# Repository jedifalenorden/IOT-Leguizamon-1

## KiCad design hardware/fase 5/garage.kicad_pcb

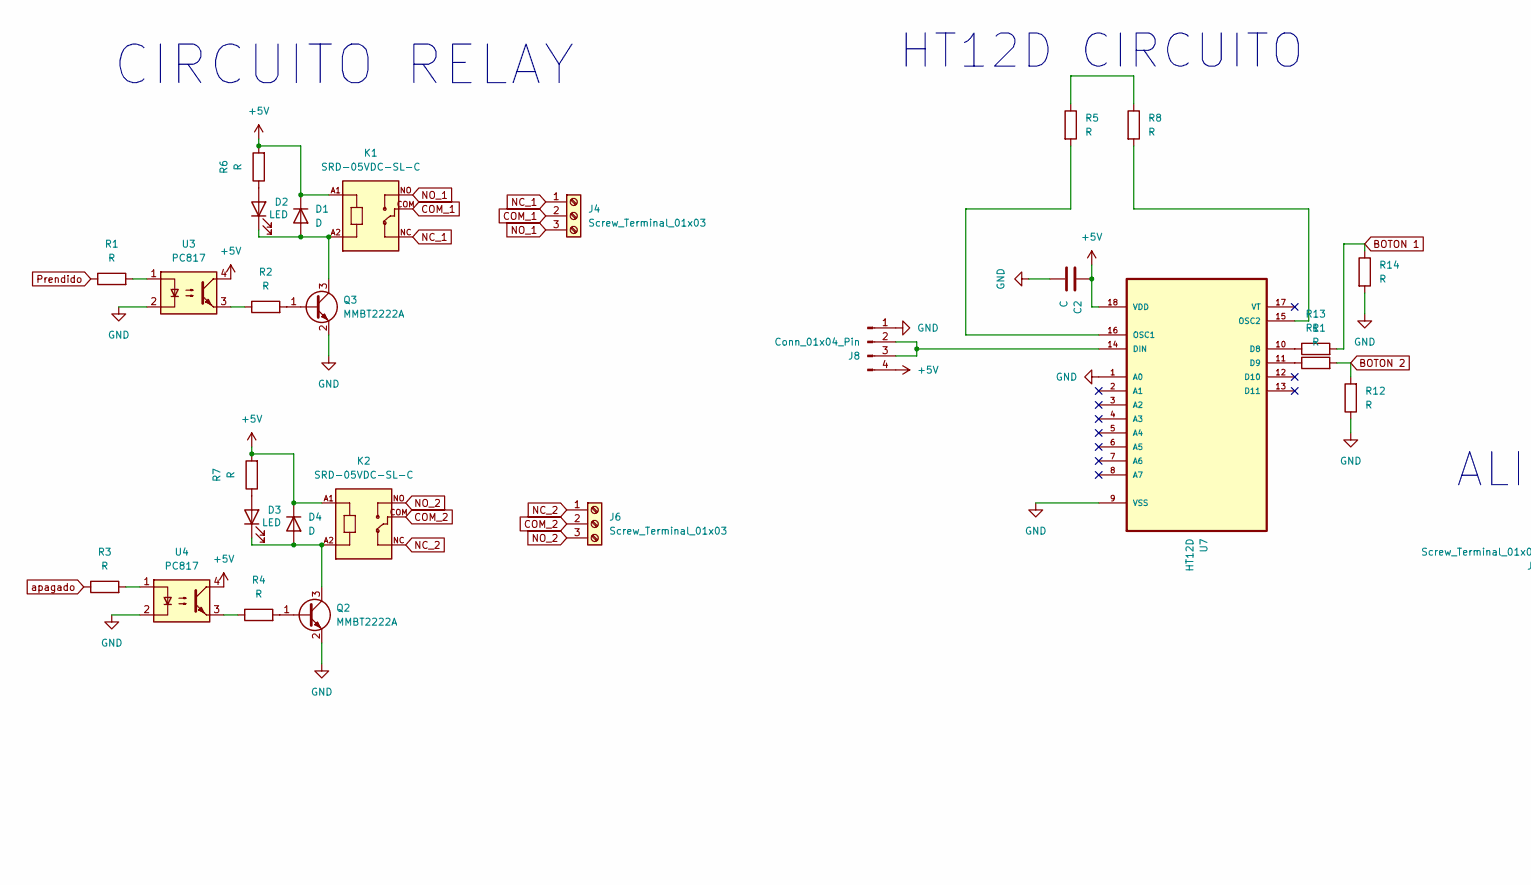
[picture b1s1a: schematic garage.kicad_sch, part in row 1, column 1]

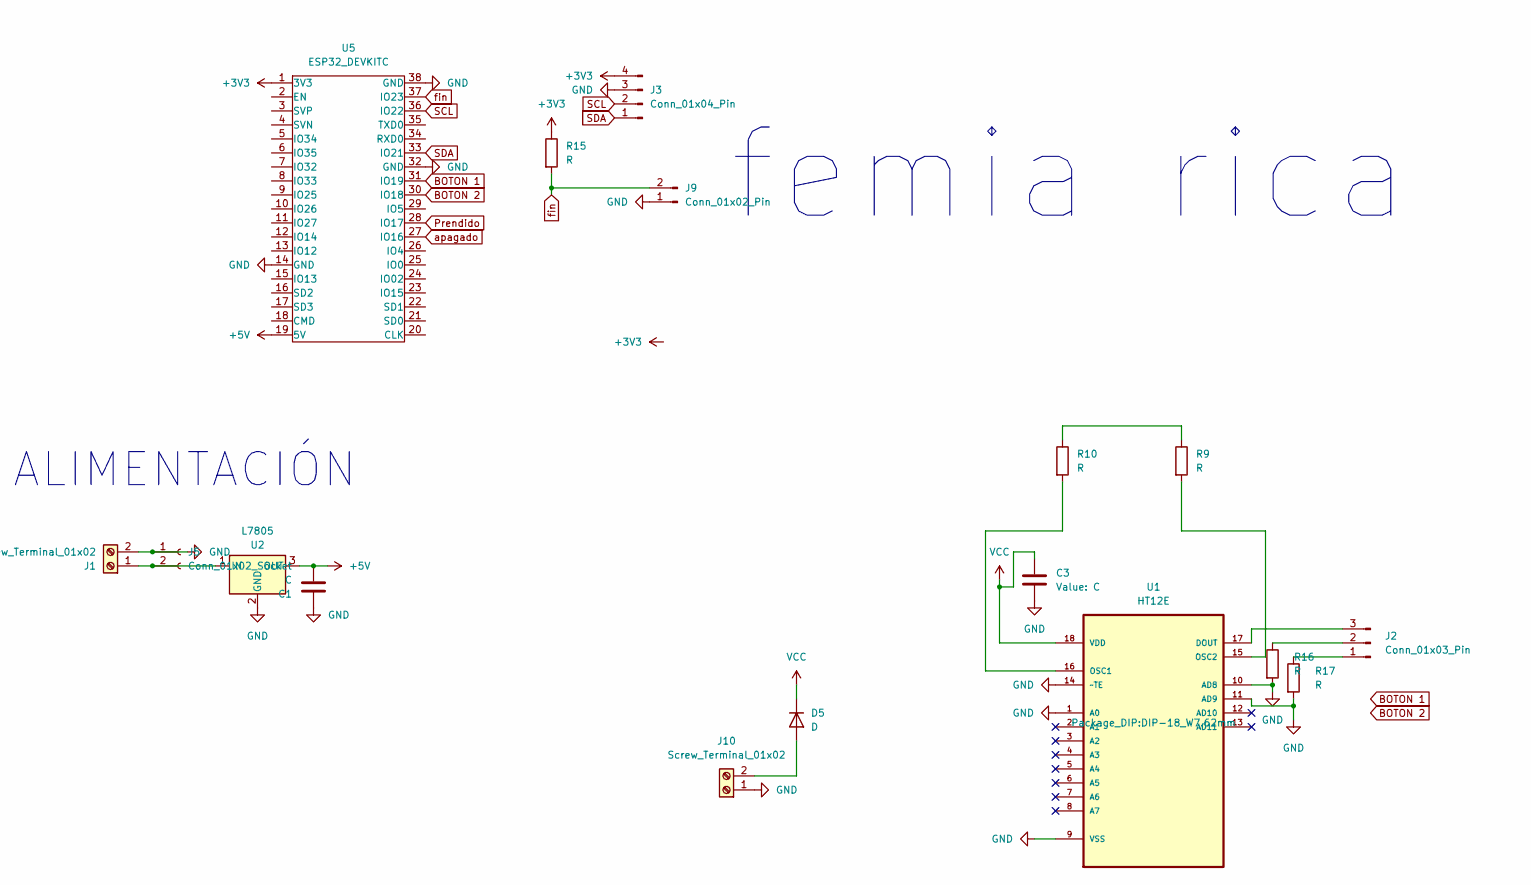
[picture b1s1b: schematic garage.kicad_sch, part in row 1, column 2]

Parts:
C1, C2, C3: C; C_0805
D1, D4: D; DO-41
D2, D3: LED; LED_D3.0mm
D5: D; D_0805_2012Metric
J1: Screw_Terminal_01x02; AMASS_XT30U-F_1x02_P5.0mm_Vertical
J2: Conn_01x03_Pin; PinHeader_1x03_P2.54mm_Vertical
J3, J8: Conn_01x04_Pin; PinHeader_1x04_P2.54mm_Vertical
J4, J6: Screw_Terminal_01x03; TerminalBlock_MetzConnect_Type011_RT05503HBWC_1x03_P5.00mm_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
J5: Conn_01x02_Socket; PinHeader_1x02_P2.00mm_Vertical
J9: Conn_01x02_Pin; PinHeader_1x02_P2.54mm_Vertical
J10: Screw_Terminal_01x02; BORNERA2_AZUL
K1, K2: SRD-05VDC-SL-C; RELAY_SRD-05VDC-SL-C
Q2, Q3: MMBT2222A; SOT-23
R1, R2, R3, R4, R5, R6, R7, R8, R9, R10, R11, R12, R13, R14, R15, R16, R17: R; R_0805
U1: HT12E; DIP-18_W7.62mm; MPN HT12E
U2: L7805; TO-263-3_TabPin2
U3, U4: PC817; DIP-4_W7.62mm
U5: ESP32_DEVKITC; esp32 38 pin
U7: HT12D; DIP-18_W7.62mm; MPN HT12D

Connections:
+3V3: J3.4, R15.1, U5.1 (3V3)
+5V: C1.2, C2.1, D1.1 (K), D4.1 (K), J8.4, K1.A1, K2.A1, R6.2, R7.2, U2.3 (OUT), U3.4, U4.4, U5.19 (5V), U7.18 (VDD)
BOTON 1: R13.2, R14.1, U5.31 (IO19)
BOTON 2: R11.2, R12.2, U5.30 (IO18)
COM_1: J4.2, K1.COM
COM_2: J6.2, K2.COM
GND: C1.1, C2.2, C3.2, J1.2, J3.3, J5.1, J8.1, J9.1, J10.1, Q2.2 (E), Q3.2 (E), R12.1, R14.2, R16.2, R17.2, U1.1 (A0), U1.9 (VSS), U1.10 (AD8), U1.11 (AD9), U1.14 (~TE), U2.2 (GND), U3.2, U4.2, U5.14 (GND), U5.32 (GND), U5.38 (GND), U7.1 (A0), U7.9 (VSS)
NC_1: J4.1, K1.NC
NC_2: J6.1, K2.NC
NO_1: J4.3, K1.NO
NO_2: J6.3, K2.NO
unnamed: D1.2 (A), D2.1 (K), K1.A2, Q3.3 (C)
unnamed: D2.2 (A), R6.1
unnamed: D3.2 (A), R7.1
unnamed: D3.1 (K), D4.2 (A), K2.A2, Q2.3 (C)
unnamed: D5.2 (A), J10.2
unnamed: J1.1, J5.2, U2.1 (IN)
unnamed: J2.1, R17.1
unnamed: J2.2, R16.1
unnamed: J2.3, U1.17 (DOUT)
unnamed: J8.2, J8.3, U7.14 (DIN)
unnamed: Q2.1 (B), R4.2
unnamed: Q3.1 (B), R2.2
unnamed: R1.2, U3.1
unnamed: R2.1, U3.3
unnamed: R3.2, U4.1
unnamed: R4.1, U4.3
unnamed: R5.1, R8.1
unnamed: R9.1, R10.1
unnamed: R10.2, U1.16 (OSC1)
unnamed: R9.2, U1.15 (OSC2)
unnamed: R13.1, U7.10 (D8)
unnamed: R11.1, U7.11 (D9)
unnamed: R5.2, U7.16 (OSC1)
unnamed: R8.2, U7.15 (OSC2)
Prendido: R1.1, U5.28 (IO17)
SCL: J3.2, U5.36 (IO22)
SDA: J3.1, U5.33 (IO21)
VCC: C3.1, D5.1 (K), U1.18 (VDD)
apagado: R3.1, U5.27 (IO16)
fin: J9.2, R15.2, U5.37 (IO23)

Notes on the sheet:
ALIMENTACIÓN
femia rica
CIRCUITO RELAY
HT12D CIRCUITO

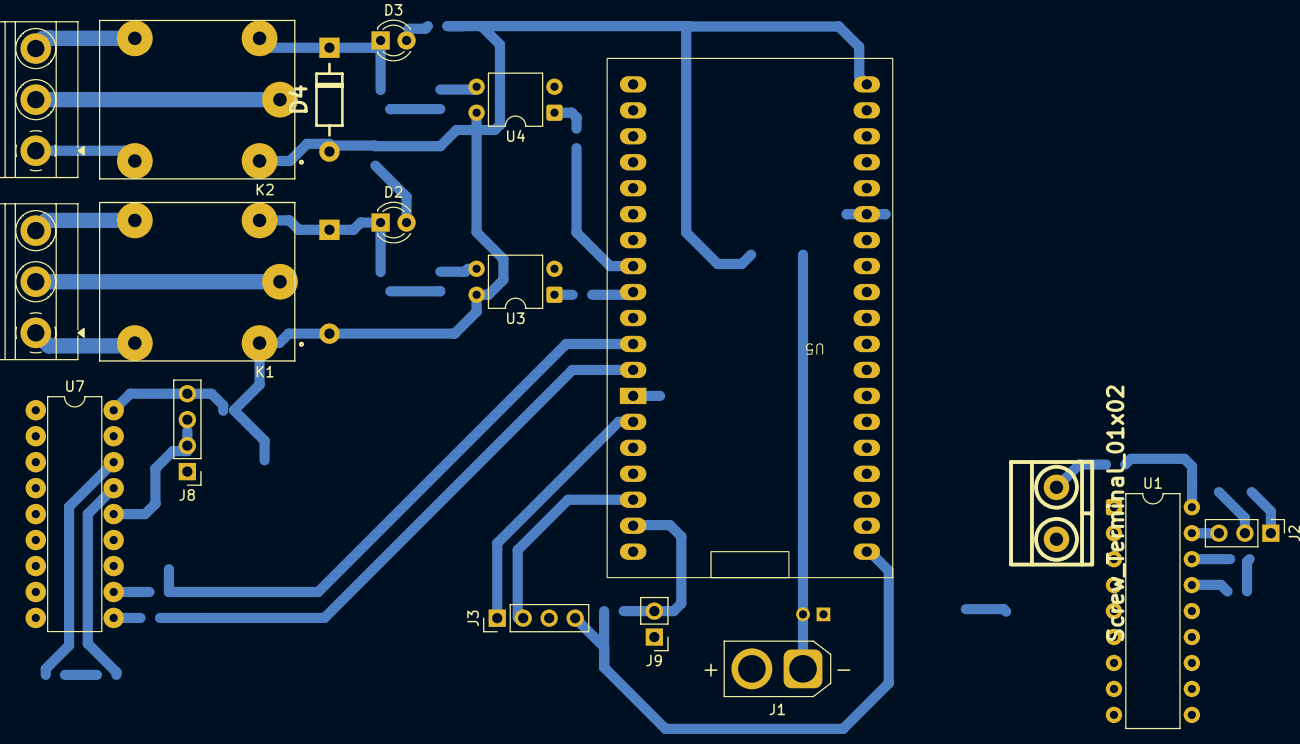
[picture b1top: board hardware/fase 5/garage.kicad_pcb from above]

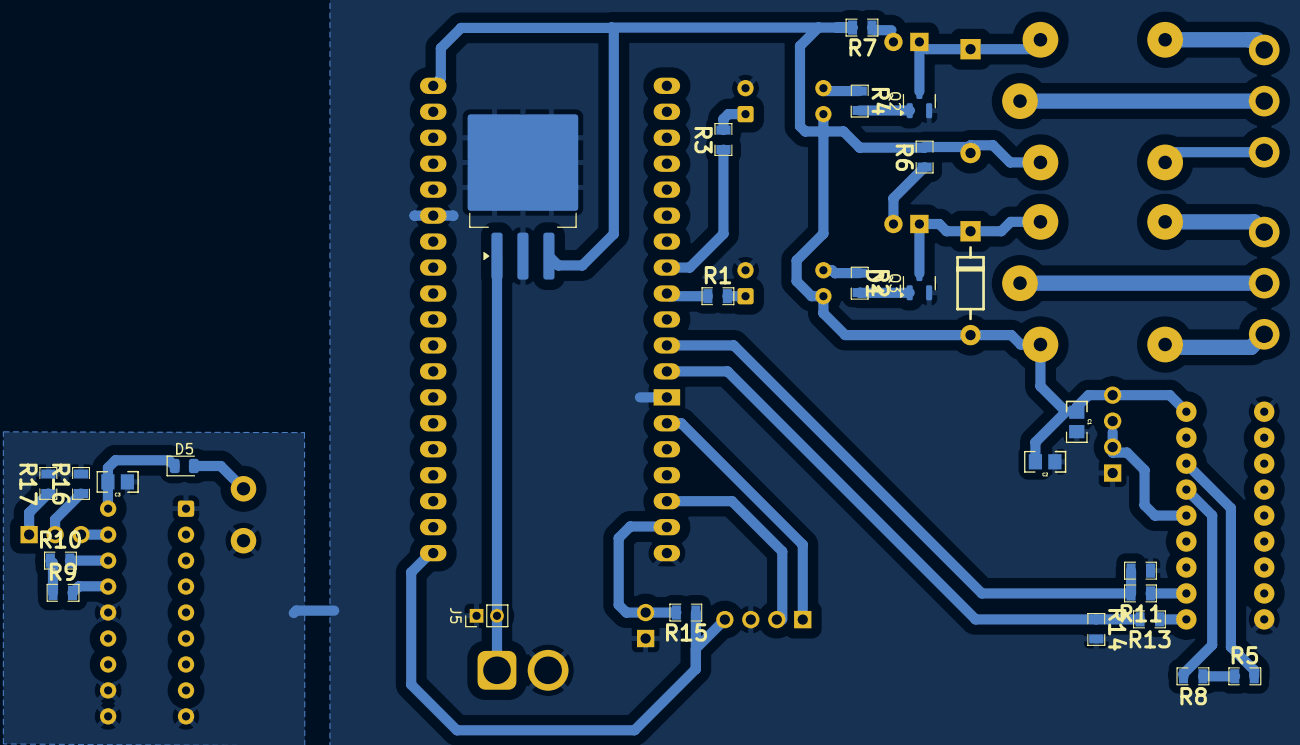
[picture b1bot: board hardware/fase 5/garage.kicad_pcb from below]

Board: 2 copper layers, 44 parts (26 on the bottom side), 41 nets.

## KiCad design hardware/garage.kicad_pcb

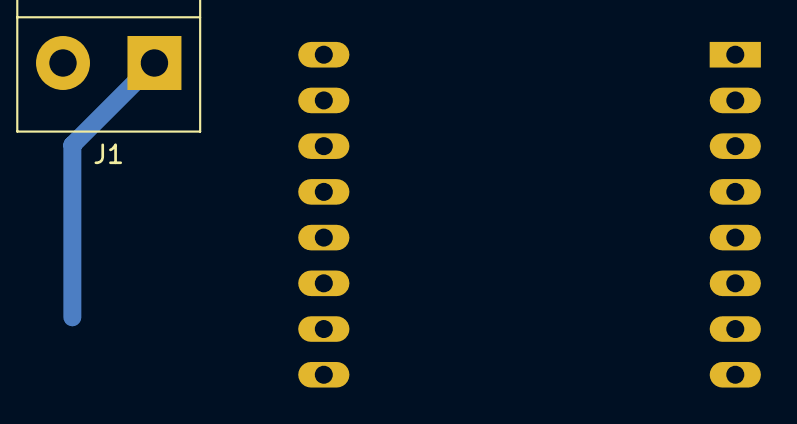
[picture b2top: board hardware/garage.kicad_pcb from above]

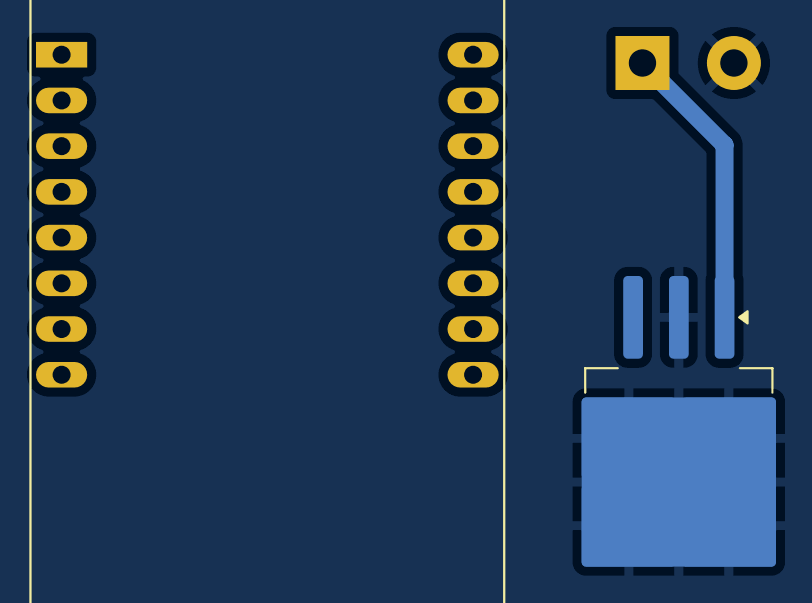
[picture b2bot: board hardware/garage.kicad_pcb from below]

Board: 2 copper layers, 3 parts (2 on the bottom side), 2 nets.

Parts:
J1: Screw_Terminal_01x02; TerminalBlock_bornier-2_P5.08mm
U1: ESP32-CAM; ESP32S-CAM
U2: L7805; TO-263-3_TabPin2

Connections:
GND: J1.2, U2.2 (GND)
unnamed: J1.1, U2.1 (IN)
